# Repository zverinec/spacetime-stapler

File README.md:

# Spacetime stapler

All the materials for the Spacetime stapler game

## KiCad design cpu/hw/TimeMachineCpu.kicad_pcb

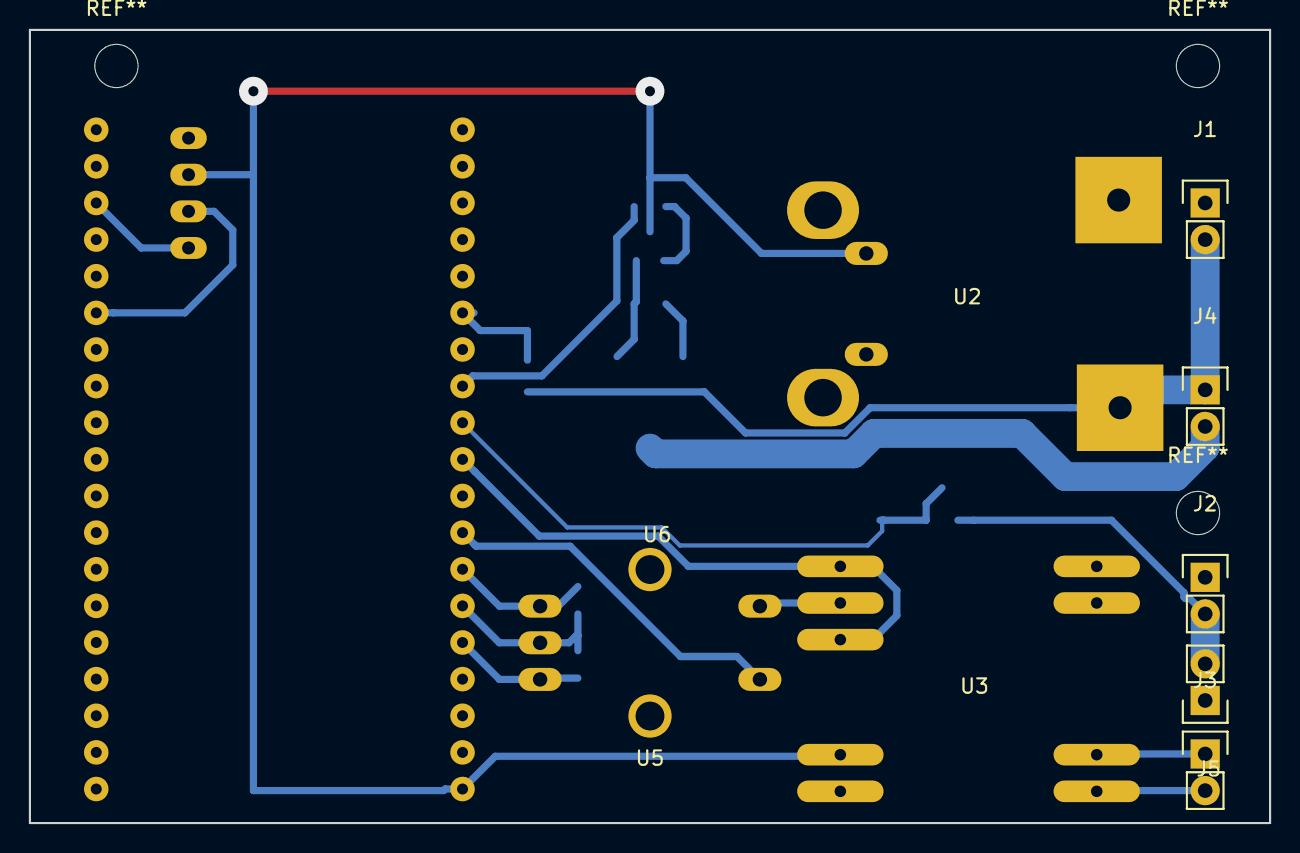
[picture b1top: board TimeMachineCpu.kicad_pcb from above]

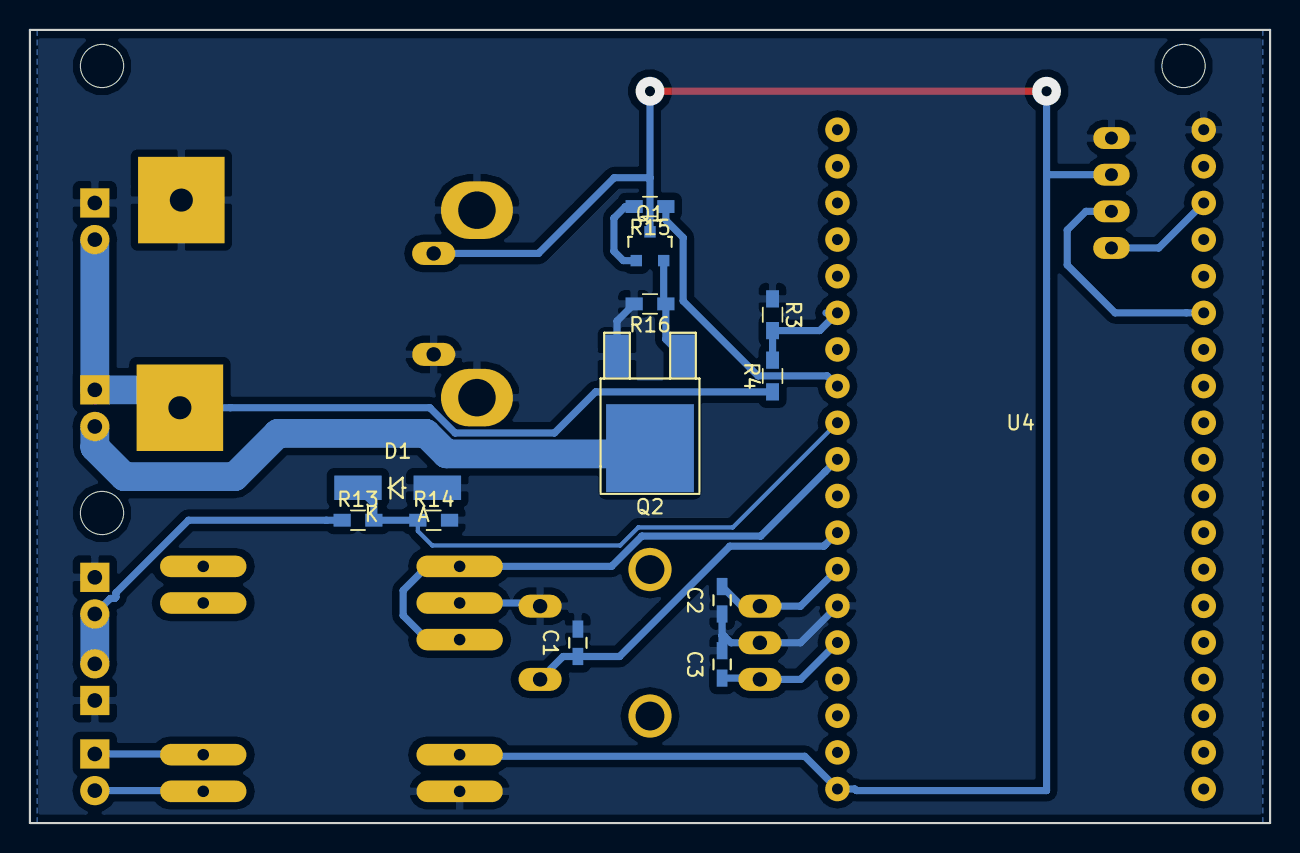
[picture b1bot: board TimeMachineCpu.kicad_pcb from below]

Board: 2 copper layers, 86.0 x 55.0 mm, 22 parts (13 on the bottom side), 18 nets.

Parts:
C1, C2, C3: 100n; C_0603_HandSoldering
D1: 3V3; MiniMELF_Handsoldering
J1: PWR_IN; Pin_Header_Straight_1x02
J2: LOAD_IN; Pin_Header_Straight_1x02
J3: SPEAKER; Pin_Header_Straight_1x02
J4: MOTOR; Pin_Header_Straight_1x02
J5: EXTERNAL_LOAD; Pin_Header_Straight_1x02
Q1: BC817; SOT-23
Q2: Q_NMOS_GDS; TO-252-2Lead
R3, R4, R13, R14: 20k; R_0603_HandSoldering
R15: 330R; R_0603_HandSoldering
R16: 1k; R_0603_HandSoldering
U2: 5VEbayStepup
U3: AudioAmp; ChineseAudioAmp
U4: ESP32-DEVKIT-C
U5: Encoder; RotationalEncoder
U6: I2C_LCD; I2C_LCD_16x2

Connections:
+5V: Q1.3, U2.3, U3.4, U4.19, U6.2
+BATT: J1.2, J4.1, R4.1, U2.1
A: C2.2, U4.13, U5.1
B: C3.1, U4.15, U5.3
BAT_SENSE: R3.2, R4.2, U4.6
BTN: C1.1, U4.12, U5.5
LOAD_1: C1.2, C2.1, C3.2, D1.2, J1.1, J2.1, J5.1, Q2.3, R3.1, R14.2, R16.2, U2.2, U2.4, U3.2, U3.5, U4.14, U4.38, U5.2, U5.4, U6.1
LOAD_2: J2.2, J5.2, R13.1
LOAD_SENSE: D1.1, R13.2, R14.1, U4.9
MOTOR_CTL: R15.1, U4.8
unnamed: J3.1, U3.7
unnamed: J3.2, U3.6
unnamed: J4.2, Q2.2
unnamed: Q1.1, R15.2
unnamed: Q1.2, Q2.1, R16.1
unnamed: U3.1, U3.3, U4.10
unnamed: U4.33, U6.3
unnamed: U4.36, U6.4

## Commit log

2018-08-14 Add buttons prototype
2018-08-14 Add lame readme for the buttons
2018-08-16 Add very simple styling
2018-08-20 Listen on everything
2018-08-20 Support Raspberry PI button
2018-08-22 Show red light at startup
2018-08-22 Add support for changing press_tolerance
2018-08-22 Add activation codes
2018-08-22 Improve button web information
2018-08-22 Update passwords
2018-08-23 Migrate CPU FW to this repository
2018-08-23 Migrate CPU HW to this repository
2018-08-23 Show user the button was pressed
2018-08-23 Get the decision time from server
2018-08-23 Respond faster to revealed secret
2019-02-22 Commit new codes
2019-02-22 Fix (we need 16-place code)
2019-06-25 Update soundtrack
2019-06-25 Implement screen turn on/off
2019-06-25 Add firmware for the Arduino for the hand-chain task
2019-06-26 Tweak the buttons response a little
2019-06-26 Tweak again
2019-06-26 Implement button turn off
2019-06-26 Fix button turn off
2019-06-26 New codes (10-Z)
2019-06-26 Implement customizable messages
2019-06-26 Run status info in a separate thread
2019-06-26 Return response on turn on/off
2020-07-21 Add brontici CPU Fw
2023-02-17 Add missing import.
2023-02-17 Add show_code.py.
